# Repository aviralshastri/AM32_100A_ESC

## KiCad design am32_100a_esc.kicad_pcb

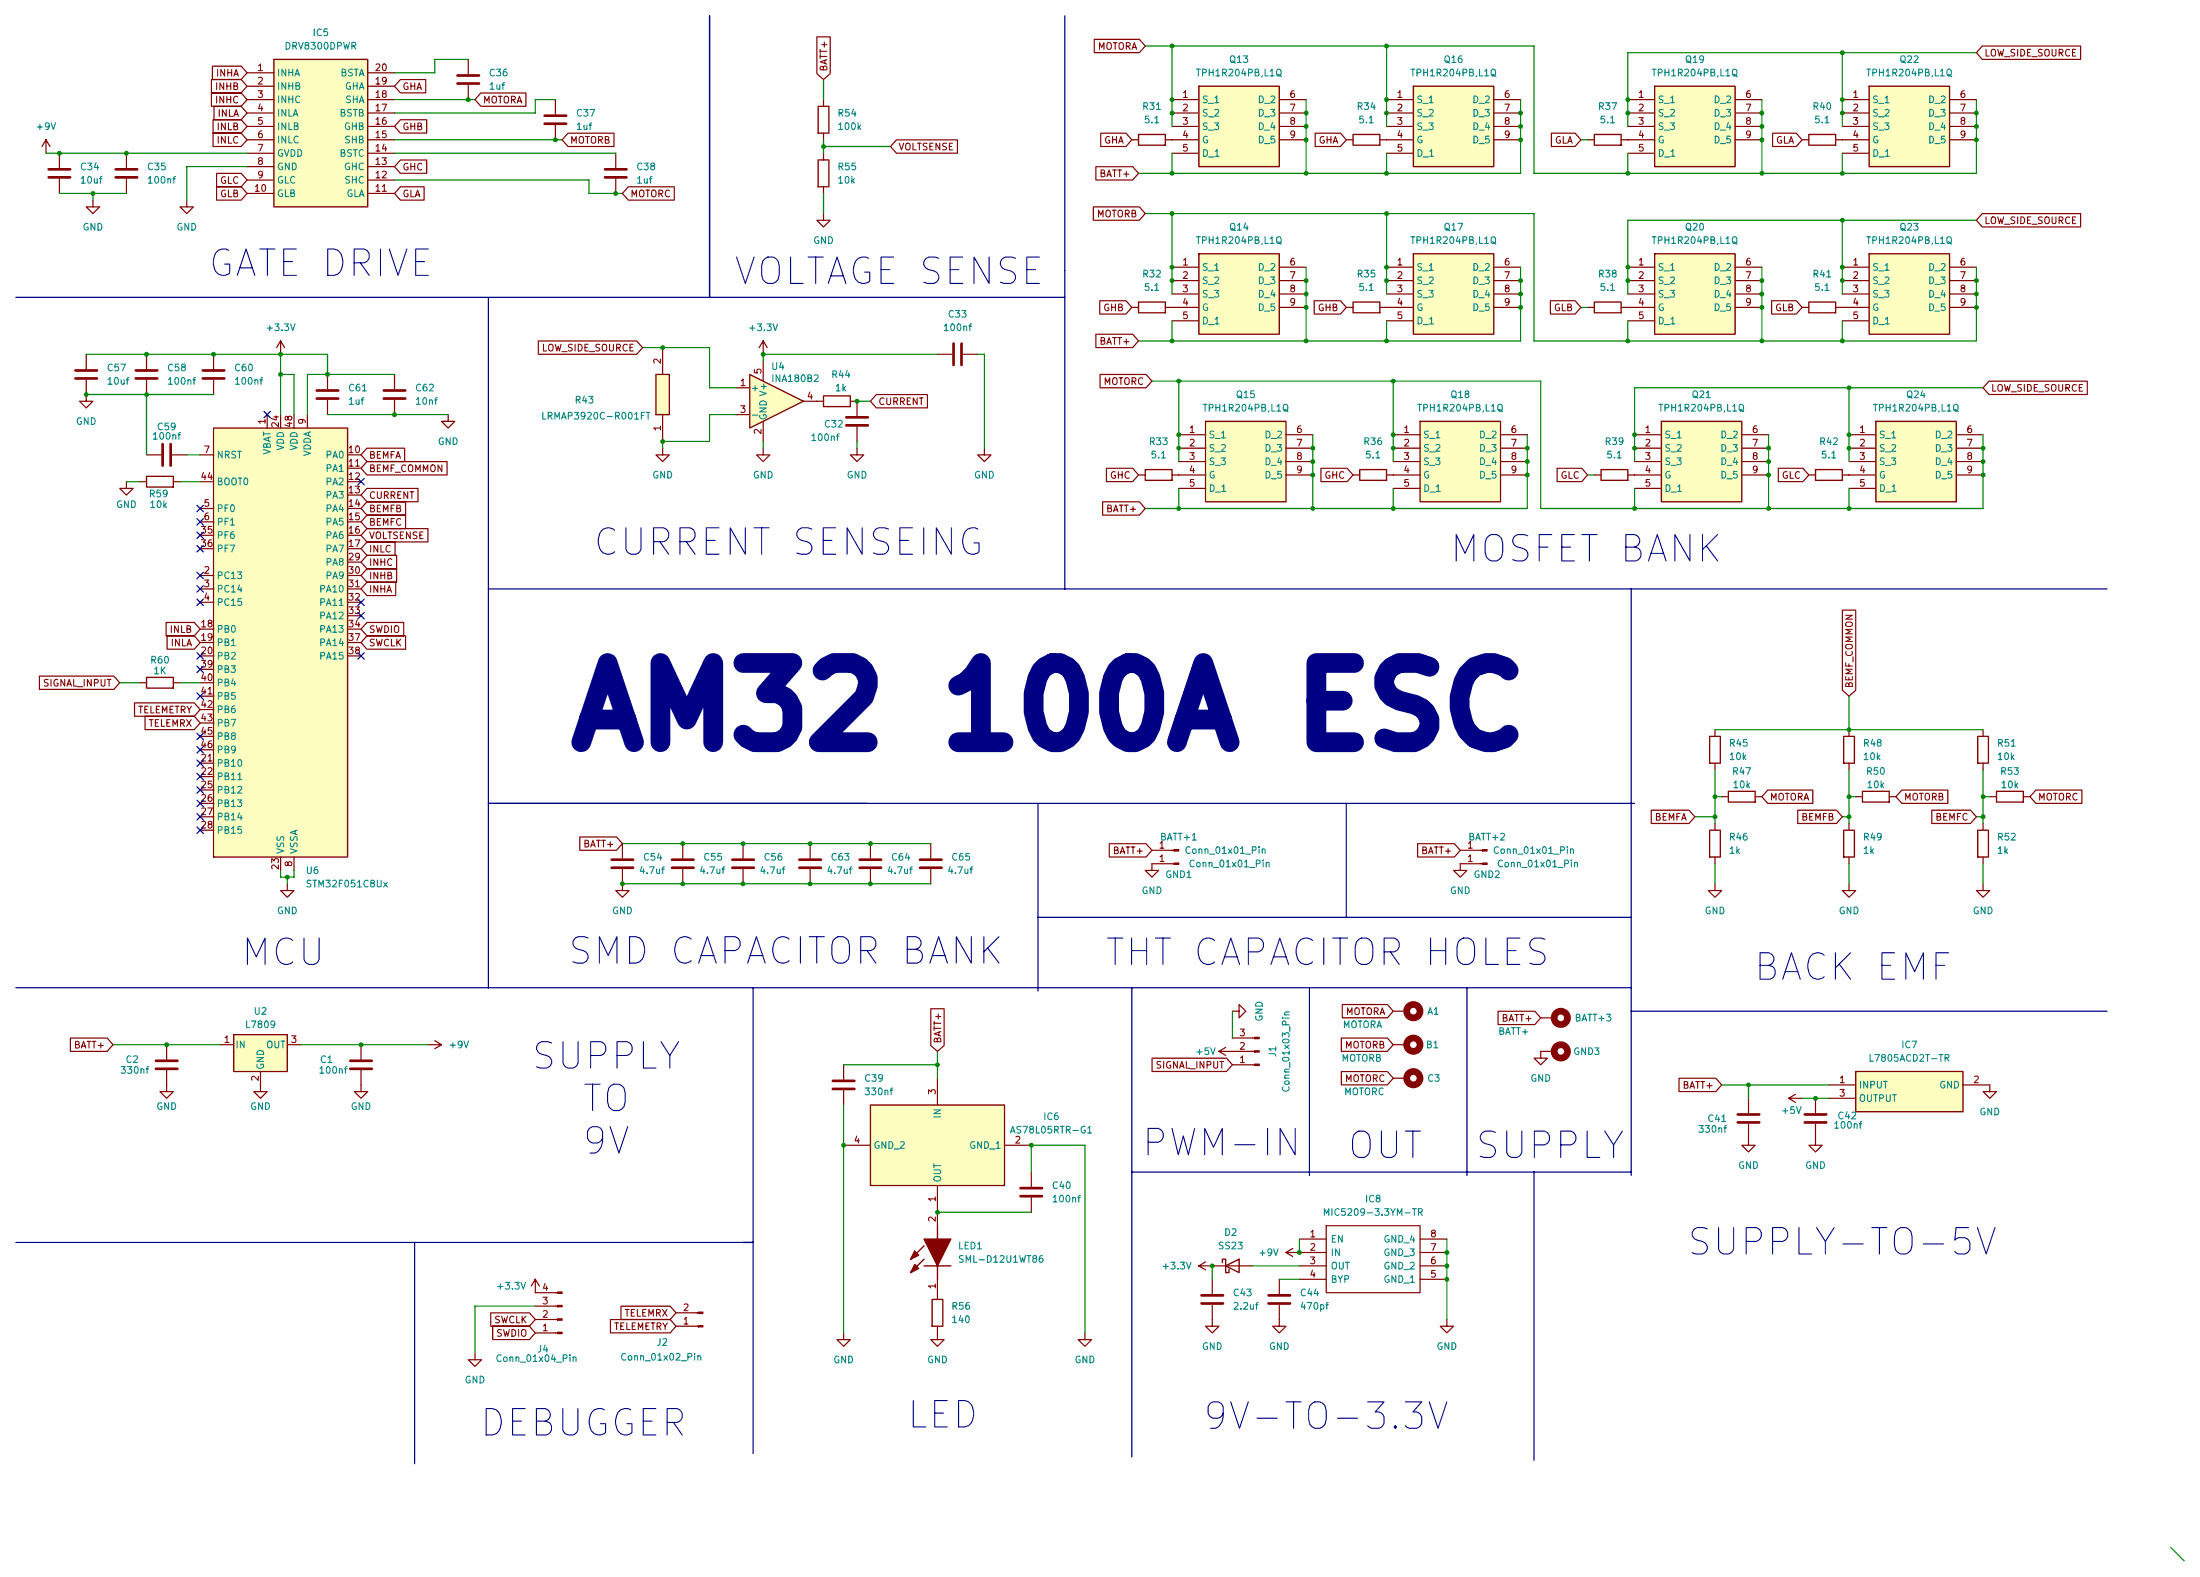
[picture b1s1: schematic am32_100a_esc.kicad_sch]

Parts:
A1: MOTORA; MountingHole_3.7mm_Pad_Via
B1: MOTORB; MountingHole_3.7mm_Pad_Via
BATT+1, BATT+2: Conn_01x01_Pin; capacitor_hole_custom
BATT+3: BATT+; MountingHole_4.3mm_M4_Pad_Via
C1, C32, C33, C35, C58, C59, C60: 100nf; C_0603_1608Metric
C2: 330nf; C_0603_1608Metric
C3: MOTORC; MountingHole_3.7mm_Pad_Via
C34, C57: 10uf; C_0603_1608Metric
C36, C37, C38: 1uf; C_1206_3216Metric
C39, C41: 330nf; C_0805_2012Metric
C40, C42: 100nf; C_0402_1005Metric
C43: 2.2uf; C_0603_1608Metric
C44: 470pf; C_0603_1608Metric
C54, C55, C56, C63, C64, C65: 4.7uf; C_1210_3225Metric
C61: 1uf; C_0603_1608Metric
C62: 10nf; C_0603_1608Metric
D2: SS23; D_SMA
GND1, GND2: Conn_01x01_Pin; capacitor_hole_custom
GND3: GND; MountingHole_4.3mm_M4_Pad_Via
IC5: DRV8300DPWR; SOP65P640X120-20N; Manufacturer_Part_Number DRV8300DPWR; Mouser Part Number 595-DRV8300DPWR
IC6: AS78L05RTR-G1; ZXTP19060CZTA; Manufacturer_Part_Number AS78L05RTR-G1; Mouser Part Number 621-AS78L05RTR-G1
IC7: L7805ACD2T-TR; TO-263-2; Manufacturer_Part_Number L7805ACD2T-TR; Mouser Part Number 511-L7805ACD2T-TR
IC8: MIC5209-3.3YM-TR; SOIC127P599X173-8N; Manufacturer_Part_Number MIC5209-3.3YM-TR; Mouser Part Number 998-MIC5209-3.3YMTR
J1: Conn_01x03_Pin; PinHeader_1x03_P2.54mm_Vertical
J2: Conn_01x02_Pin; PinHeader_1x02_P2.54mm_Vertical
J4: Conn_01x04_Pin; PinHeader_1x04_P2.54mm_Vertical
LED1: SML-D12U1WT86; LEDC1608X65N; Manufacturer_Part_Number SML-D12U1WT86; Mouser Part Number 755-SML-D12U1WT86
Q13, Q14, Q15, Q16, Q17, Q18, Q19, Q20, Q21, Q22, Q23, Q24: TPH1R204PB,L1Q; TPH1R306PLL1Q; Manufacturer_Part_Number TPH1R204PB,L1Q; Mouser Part Number 757-TPH1R204PBL1Q
R31, R32, R33, R34, R35, R36, R37, R38, R39, R40, R41, R42: 5.1; R_0402_1005Metric
R43: LRMAP3920C-R001FT; RESC10052X136N; Mouser Part Number 66-LRMAP3920C-R001FT
R44, R46, R49, R52: 1k; R_0402_1005Metric
R45, R47, R48, R50, R51, R53, R59: 10k; R_0402_1005Metric
R54: 100k; R_0603_1608Metric
R55: 10k; R_0603_1608Metric
R56: 140; R_0402_1005Metric
R60: 1K; R_0402_1005Metric
U2: L7809; TO-263-2
U4: INA180B2; SOT-23-5
U6: STM32F051C8Ux; QFN-48-1EP_7x7mm_P0.5mm_EP5.6x5.6mm

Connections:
+3.3V: C33.1, C43.1, C57.1, C58.1, C60.1, C61.1, C62.1, D2.1 (K), J4.4, U4.5 (V+), U6.9 (VDDA), U6.24 (VDD), U6.48 (VDD)
+5V: C42.1, IC7.3 (OUTPUT), J1.2
+9V: C1.1, C34.1, C35.1, IC5.7 (GVDD), IC8.1 (EN), IC8.2 (IN), U2.3 (OUT)
BATT+: BATT+1.1 (Pin_1_1), BATT+2.1 (Pin_1_1), BATT+3.1 (1_1), C2.1, C39.1, C41.1, C54.1, C55.1, C56.1, C63.1, C64.1, C65.1, IC6.3 (IN), IC7.1 (INPUT), Q13.5 (D_1), Q13.6 (D_2), Q13.7 (D_3), Q13.8 (D_4), Q13.9 (D_5), Q14.5 (D_1), Q14.6 (D_2), Q14.7 (D_3), Q14.8 (D_4), Q14.9 (D_5), Q15.5 (D_1), Q15.6 (D_2), Q15.7 (D_3), Q15.8 (D_4), Q15.9 (D_5), Q16.5 (D_1), Q16.6 (D_2), Q16.7 (D_3), Q16.8 (D_4), Q16.9 (D_5), Q17.5 (D_1), Q17.6 (D_2), Q17.7 (D_3), Q17.8 (D_4), Q17.9 (D_5), Q18.5 (D_1), Q18.6 (D_2), Q18.7 (D_3), Q18.8 (D_4), Q18.9 (D_5), R54.1, U2.1 (IN)
BEMFA: R45.2, R46.1, R47.1, U6.10 (PA0)
BEMFB: R48.2, R49.1, R50.1, U6.14 (PA4)
BEMFC: R51.2, R52.1, R53.1, U6.15 (PA5)
BEMF_COMMON: R45.1, R48.1, R51.1, U6.11 (PA1)
CURRENT: C32.1, R44.2, U6.13 (PA3)
GHA: IC5.19 (GHA), R31.1, R34.1
GHB: IC5.16 (GHB), R32.1, R35.1
GHC: IC5.13 (GHC), R33.1, R36.1
GLA: IC5.11 (GLA), R37.1, R40.1
GLB: IC5.10 (GLB), R38.1, R41.1
GLC: IC5.9 (GLC), R39.1, R42.1
GND: C1.2, C2.2, C32.2, C33.2, C34.2, C35.2, C39.2, C40.1, C41.2, C42.2, C43.2, C44.2, C54.2, C55.2, C56.2, C57.2, C58.2, C59.2, C60.2, C61.2, C62.2, C63.2, C64.2, C65.2, GND1.1 (Pin_1_1), GND2.1 (Pin_1_1), GND3.1 (1_1), IC5.8 (GND), IC6.2 (GND_1), IC6.4 (GND_2), IC7.2 (GND), IC8.5 (GND_1), IC8.6 (GND_2), IC8.7 (GND_3), IC8.8 (GND_4), J1.3, J4.3, R43.1, R46.2, R49.2, R52.2, R55.2, R56.2, R59.1, U2.2 (GND), U4.2 (GND), U4.3 (-), U6.8 (VSSA), U6.23 (VSS), U6.47 (VSS), U6.49 (VSS)
INHA: IC5.1 (INHA), U6.31 (PA10)
INHB: IC5.2 (INHB), U6.30 (PA9)
INHC: IC5.3 (INHC), U6.29 (PA8)
INLA: IC5.4 (INLA), U6.19 (PB1)
INLB: IC5.5 (INLB), U6.18 (PB0)
INLC: IC5.6 (INLC), U6.17 (PA7)
LOW_SIDE_SOURCE: Q19.1 (S_1), Q19.2 (S_2), Q19.3 (S_3), Q20.1 (S_1), Q20.2 (S_2), Q20.3 (S_3), Q21.1 (S_1), Q21.2 (S_2), Q21.3 (S_3), Q22.1 (S_1), Q22.2 (S_2), Q22.3 (S_3), Q23.1 (S_1), Q23.2 (S_2), Q23.3 (S_3), Q24.1 (S_1), Q24.2 (S_2), Q24.3 (S_3), R43.2, U4.1 (+)
MOTORA: A1.1 (1_1), C36.2, IC5.18 (SHA), Q13.1 (S_1), Q13.2 (S_2), Q13.3 (S_3), Q16.1 (S_1), Q16.2 (S_2), Q16.3 (S_3), Q19.5 (D_1), Q19.6 (D_2), Q19.7 (D_3), Q19.8 (D_4), Q19.9 (D_5), Q22.5 (D_1), Q22.6 (D_2), Q22.7 (D_3), Q22.8 (D_4), Q22.9 (D_5), R47.2
MOTORB: B1.1 (1_1), C37.2, IC5.15 (SHB), Q14.1 (S_1), Q14.2 (S_2), Q14.3 (S_3), Q17.1 (S_1), Q17.2 (S_2), Q17.3 (S_3), Q20.5 (D_1), Q20.6 (D_2), Q20.7 (D_3), Q20.8 (D_4), Q20.9 (D_5), Q23.5 (D_1), Q23.6 (D_2), Q23.7 (D_3), Q23.8 (D_4), Q23.9 (D_5), R50.2
MOTORC: C3.1 (1_1), C38.2, IC5.12 (SHC), Q15.1 (S_1), Q15.2 (S_2), Q15.3 (S_3), Q18.1 (S_1), Q18.2 (S_2), Q18.3 (S_3), Q21.5 (D_1), Q21.6 (D_2), Q21.7 (D_3), Q21.8 (D_4), Q21.9 (D_5), Q24.5 (D_1), Q24.6 (D_2), Q24.7 (D_3), Q24.8 (D_4), Q24.9 (D_5), R53.2
unnamed: D2.2 (A), IC8.3 (OUT)
unnamed: C36.1, IC5.20 (BSTA)
unnamed: C37.1, IC5.17 (BSTB)
unnamed: C38.1, IC5.14 (BSTC)
unnamed: C40.2, IC6.1 (OUT), LED1.2 (A)
unnamed: C44.1, IC8.4 (BYP)
unnamed: LED1.1 (K), R56.1
unnamed: Q13.4 (G), R31.2
unnamed: Q14.4 (G), R32.2
unnamed: Q15.4 (G), R33.2
unnamed: Q16.4 (G), R34.2
unnamed: Q17.4 (G), R35.2
unnamed: Q18.4 (G), R36.2
unnamed: Q19.4 (G), R37.2
unnamed: Q20.4 (G), R38.2
unnamed: Q21.4 (G), R39.2
unnamed: Q22.4 (G), R40.2
unnamed: Q23.4 (G), R41.2
unnamed: Q24.4 (G), R42.2
unnamed: R44.1, U4.4
unnamed: R59.2, U6.44 (BOOT0)
unnamed: C59.1, U6.7 (NRST)
unnamed: R60.2, U6.40 (PB4)
SIGNAL_INPUT: J1.1, R60.1
SWCLK: J4.2, U6.37 (PA14)
SWDIO: J4.1, U6.34 (PA13)
TELEMETRY: J2.1, U6.42 (PB6)
TELEMRX: J2.2, U6.43 (PB7)
VOLTSENSE: R54.2, R55.1, U6.16 (PA6)

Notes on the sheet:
MCU
OUT
VOLTAGE SENSE
PWM-IN
BACK EMF
9V-TO-3.3V
LED
GATE DRIVE
MOSFET BANK
AM32 100A ESC
SUPPLY-TO-5V
THT CAPACITOR HOLES
SUPPLY
CURRENT SENSEING
DEBUGGER
SMD CAPACITOR BANK
SUPPLY TO 9V

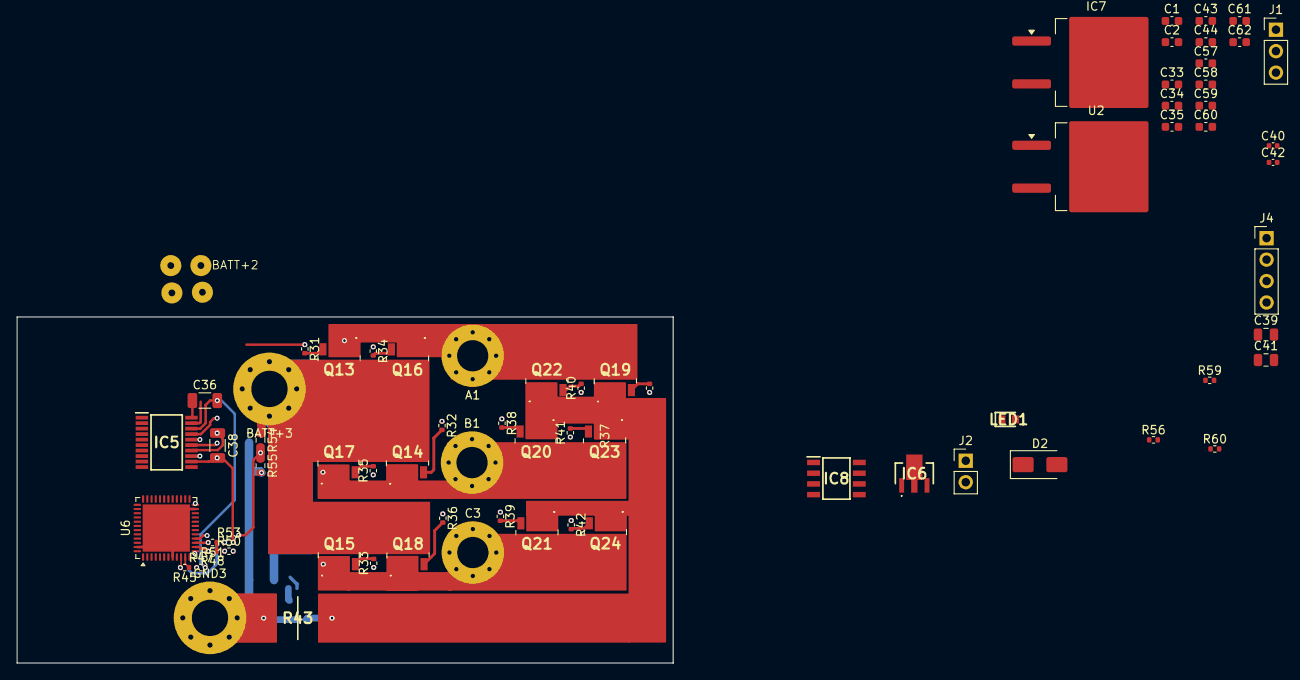
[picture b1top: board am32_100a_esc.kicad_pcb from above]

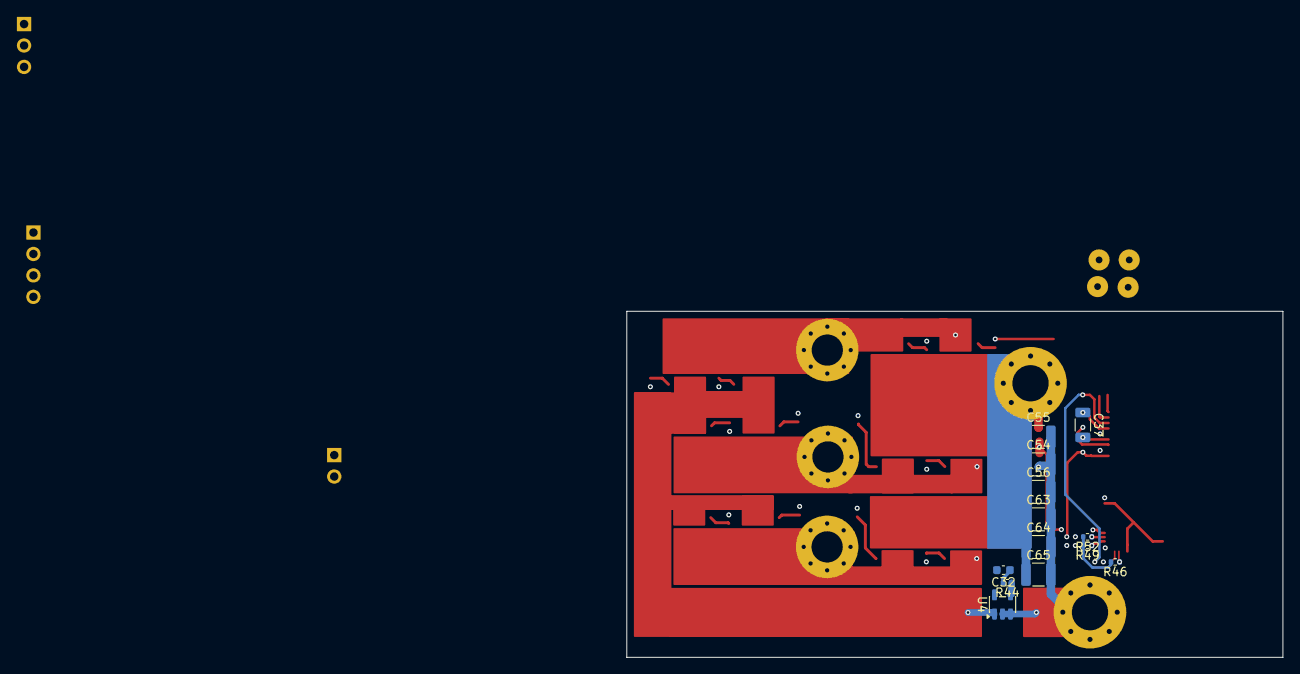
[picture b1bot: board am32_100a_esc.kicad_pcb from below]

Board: 4 copper layers, 77.7 x 41.0 mm, 88 parts (13 on the bottom side), 55 nets.

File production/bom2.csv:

"Reference","Qty","Value","DNP","Exclude from BOM","Exclude from Board","Footprint","Datasheet"
"C1,C32,C33,C35,C58,C59,C60","7","100nf","","","","Capacitor_SMD:C_0603_1608Metric",""
"C2","1","330nf","","","","Capacitor_SMD:C_0603_1608Metric",""
"C34,C57","2","10uf","","","","Capacitor_SMD:C_0603_1608Metric",""
"C36,C37,C38","3","1uf","","","","Capacitor_SMD:C_1206_3216Metric",""
"C39,C41","2","330nf","","","","Capacitor_SMD:C_0805_2012Metric",""
"C40,C42","2","100nf","","","","Capacitor_SMD:C_0402_1005Metric",""
"C43","1","2.2uf","","","","Capacitor_SMD:C_0603_1608Metric",""
"C44","1","470pf","","","","Capacitor_SMD:C_0603_1608Metric",""
"C54,C55,C56,C63,C64,C65","6","4.7uf","","","","Capacitor_SMD:C_1210_3225Metric",""
"C61","1","1uf","","","","Capacitor_SMD:C_0603_1608Metric",""
"C62","1","10nf","","","","Capacitor_SMD:C_0603_1608Metric",""
"D2","1","SS23","","","","Diode_SMD:D_SMA","https://www.vishay.com/docs/88748/ss22.pdf"
"IC5","1","DRV8300DPWR","","","","DRV8300DPWR:SOP65P640X120-20N",""
"IC6","1","AS78L05RTR-G1","","","","AS78L05RTR-G1:ZXTP19060CZTA","https://www.diodes.com//assets/Datasheets/AS78Lxx.pdf"
"IC7","1","L7805ACD2T-TR","","","","Package_TO_SOT_SMD:TO-263-2","https://www.st.com/content/ccc/resource/technical/document/d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"
"IC8","1","MIC5209-3.3YM-TR","","","","MIC5209-3.3YM-TR:SOIC127P599X173-8N","http://www.microchip.com/mymicrochip/filehandler.aspx?ddocna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"
"LED1","1","SML-D12U1WT86","","","","SML-D12U1WT86:LEDC1608X65N","https://componentsearchengine.com/Datasheets/1/SML-D12U1WT86.pdf"
"Q13,Q14,Q15,Q16,Q17,Q18,Q19,Q20,Q21,Q22,Q23,Q24","12","TPH1R204PB,L1Q","","","","TPH1R204PB,L1Q:TPH1R306PLL1Q","http://toshiba.semicon-storage.com/info/docget.jsp?did=57107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"
"R31,R32,R33,R34,R35,R36,R37,R38,R39,R40,R41,R42","12","5.1","","","","Resistor_SMD:R_0402_1005Metric",""
"R43","1","LRMAP3920C-R001FT","","","","LRMAP3920C-R001FT:RESC10052X136N","https://componentsearchengine.com/Datasheets/1/LRMAP3920C-R0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"
"R44,R46,R49,R52","4","1k","","","","Resistor_SMD:R_0402_1005Metric",""
"R45,R47,R48,R50,R51,R53,R59","7","10k","","","","Resistor_SMD:R_0402_1005Metric",""
"R54","1","100k","","","","Resistor_SMD:R_0603_1608Metric",""
"R55","1","10k","","","","Resistor_SMD:R_0603_1608Metric",""
"R56","1","140","","","","Resistor_SMD:R_0402_1005Metric",""
"R60","1","1K","","","","Resistor_SMD:R_0402_1005Metric",""
"U2","1","L7809","","","","Package_TO_SOT_SMD:TO-263-2","http://www.st.com/content/ccc/resource/technical/document/da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"
"U4","1","INA180B2","","","","Package_TO_SOT_SMD:SOT-23-5","http://www.ti.com/lit/ds/symlink/ina180.pdf"
"U6","1","STM32F051C8Ux","","","","Package_DFN_QFN:QFN-48-1EP_7x7mm_P0.5mm_EP5.6x5.6mm","https://www.st.com/resource/en/datasheet/stm32f051c8.pdf"

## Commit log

2026-05-01 schematics done
2026-05-01 removed .history file
2026-05-11 ROUTING COMPLETE
    Read for production. With Gerber
2026-05-11 dummy
    dummy
2026-05-12 added more doodles
2026-05-13 Final from my side with drc checked .
2026-05-14 re started with routing for better working and removing wrong connections
